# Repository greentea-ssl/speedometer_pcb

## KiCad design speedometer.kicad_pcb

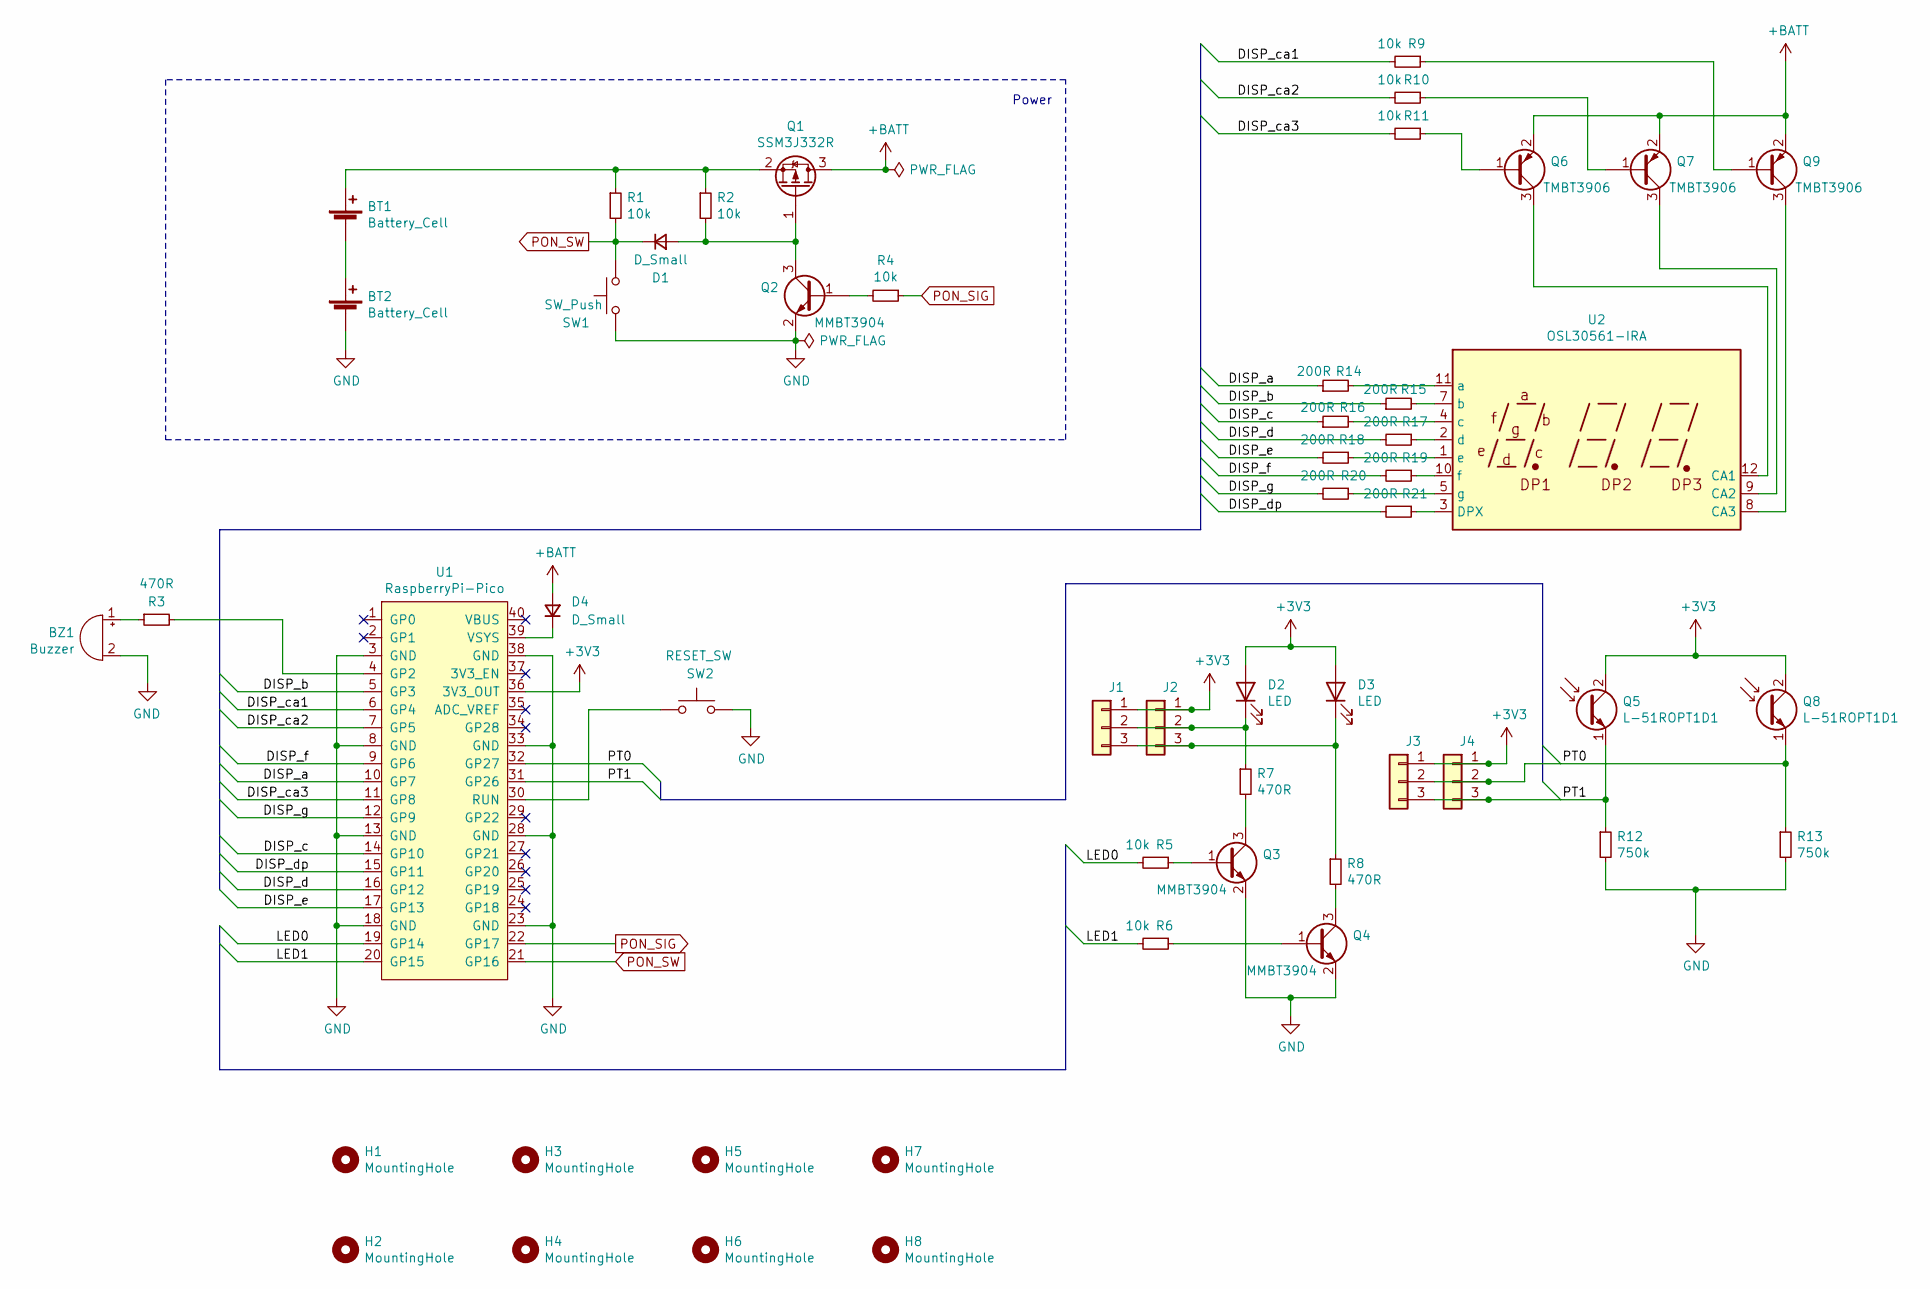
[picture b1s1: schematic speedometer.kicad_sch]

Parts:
BT1, BT2: Battery_Cell; AA-Battery
BZ1: Buzzer; Buzzer_TDK_PS1240P02BT_D12.2mm_H6.5mm
D1: D_Small; D_SOD-123
D2, D3: LED; LED_D5.0mm_IRGrey
D4: D_Small; D_0603_1608Metric
H1, H2, H3, H4, H5, H6, H7, H8: MountingHole; MountingHole_3.2mm_M3_noResist
J1, J2, J3, J4: Conn_01x03; JST_PH_S3B-PH-K_1x03_P2.00mm_Horizontal
Q1: SSM3J332R; SOT-23
Q2, Q3, Q4: MMBT3904; SOT-23
Q5, Q8: L-51ROPT1D1; LED_D5.0mm_IRBlack
Q6, Q7, Q9: TMBT3906; SOT-23
R1, R2, R4, R5, R6, R9, R10, R11: 10k; R_0603_1608Metric
R3, R7, R8: 470R; R_0603_1608Metric
R12, R13: 750k; R_0603_1608Metric
R14, R15, R16, R17, R18, R19, R20, R21: 200R; R_0603_1608Metric
SW1: SW_Push; SW_PUSH_6mm_H7.3mm
SW2: RESET_SW; SW_PUSH_6mm_H7.3mm
U1: RaspberryPi-Pico
U2: OSL30561-IRA

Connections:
+3V3: D2.2 (A), D3.2 (A), J1.1, J2.1, J3.1, J4.1, Q5.2 (C), Q8.2 (C), U1.36 (3V3_OUT)
+BATT: D4.2 (A), Q1.3 (D), Q6.2 (E), Q7.2 (E), Q9.2 (E)
/DISP_a: R14.1, U1.10 (GP7)
/DISP_b: R15.1, U1.5 (GP3)
/DISP_c: R16.1, U1.14 (GP10)
/DISP_ca1: R9.2, U1.6 (GP4)
/DISP_ca2: R10.2, U1.7 (GP5)
/DISP_ca3: R11.2, U1.11 (GP8)
/DISP_d: R17.2, U1.16 (GP12)
/DISP_dp: R21.2, U1.15 (GP11)
/DISP_e: R18.2, U1.17 (GP13)
/DISP_f: R19.2, U1.9 (GP6)
/DISP_g: R20.2, U1.12 (GP9)
/LED0: R5.2, U1.19 (GP14)
/LED1: R6.2, U1.20 (GP15)
/PT0: J3.2, J4.2, Q8.1 (E), R13.1, U1.32 (GP27)
/PT1: J3.3, J4.3, Q5.1 (E), R12.1, U1.31 (GP26)
GND: BT2.2 (-), BZ1.2 (+), Q2.2 (E), Q3.2 (E), Q4.2 (E), R12.2, R13.2, SW1.1, SW2.2, U1.3 (GND), U1.8 (GND), U1.13 (GND), U1.18 (GND), U1.23 (GND), U1.28 (GND), U1.33 (GND), U1.38 (GND)
unnamed: BT1.1 (+), Q1.2 (S), R1.1, R2.1
unnamed: BT1.2 (-), BT2.1 (+)
unnamed: BZ1.1 (-), R3.1
unnamed: D1.2 (A), Q1.1 (G), Q2.3 (C), R2.2
unnamed: D2.1 (K), J1.2, J2.2, R7.1
unnamed: D3.1 (K), J1.3, J2.3, R8.1
unnamed: D4.1 (K), U1.39 (VSYS)
unnamed: Q2.1 (B), R4.2
unnamed: Q3.1 (B), R5.1
unnamed: Q3.3 (C), R7.2
unnamed: Q4.1 (B), R6.1
unnamed: Q4.3 (C), R8.2
unnamed: Q6.1 (B), R11.1
unnamed: Q6.3 (C), U2.12 (CA1)
unnamed: Q7.1 (B), R10.1
unnamed: Q7.3 (C), U2.9 (CA2)
unnamed: Q9.1 (B), R9.1
unnamed: Q9.3 (C), U2.8 (CA3)
unnamed: R3.2, U1.4 (GP2)
unnamed: SW2.1, U1.30 (RUN)
unnamed: R21.1, U2.3 (DPX)
unnamed: R14.2, U2.11 (a)
unnamed: R15.2, U2.7 (b)
unnamed: R16.2, U2.4 (c)
unnamed: R17.1, U2.2 (d)
unnamed: R18.1, U2.1 (e)
unnamed: R19.1, U2.10 (f)
unnamed: R20.1, U2.5 (g)
PON_SIG: R4.1, U1.22 (GP17)
PON_SW: D1.1 (K), R1.2, SW1.2, U1.21 (GP16)

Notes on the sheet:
Power

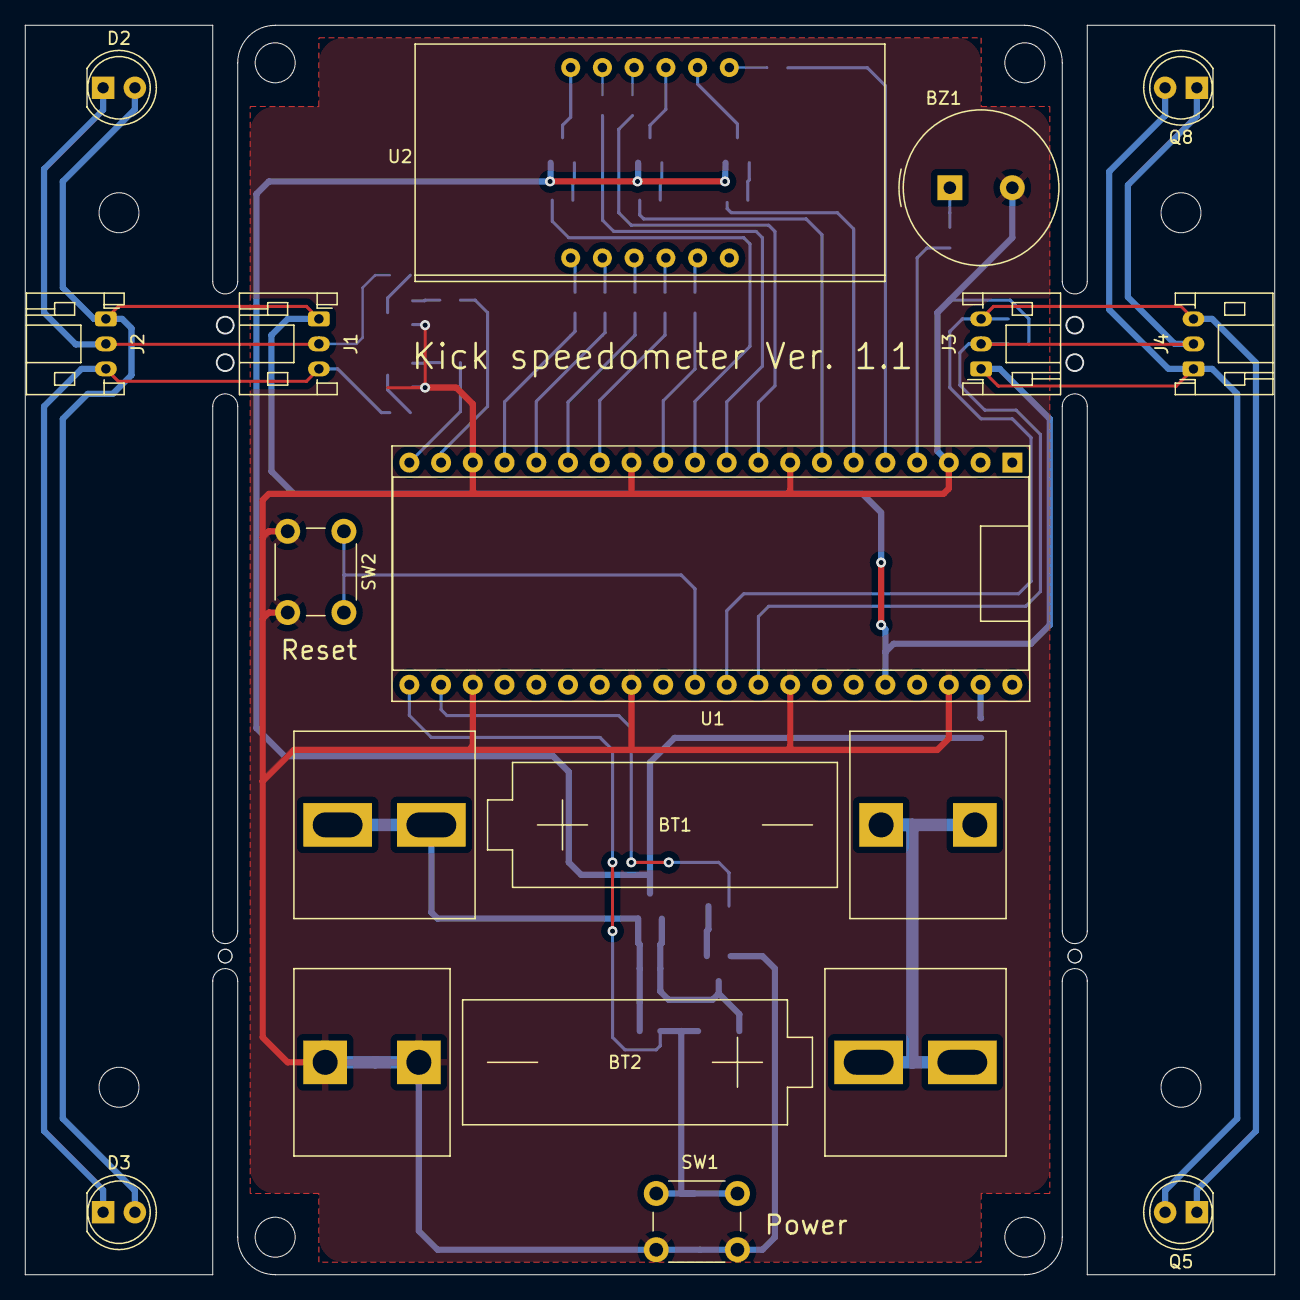
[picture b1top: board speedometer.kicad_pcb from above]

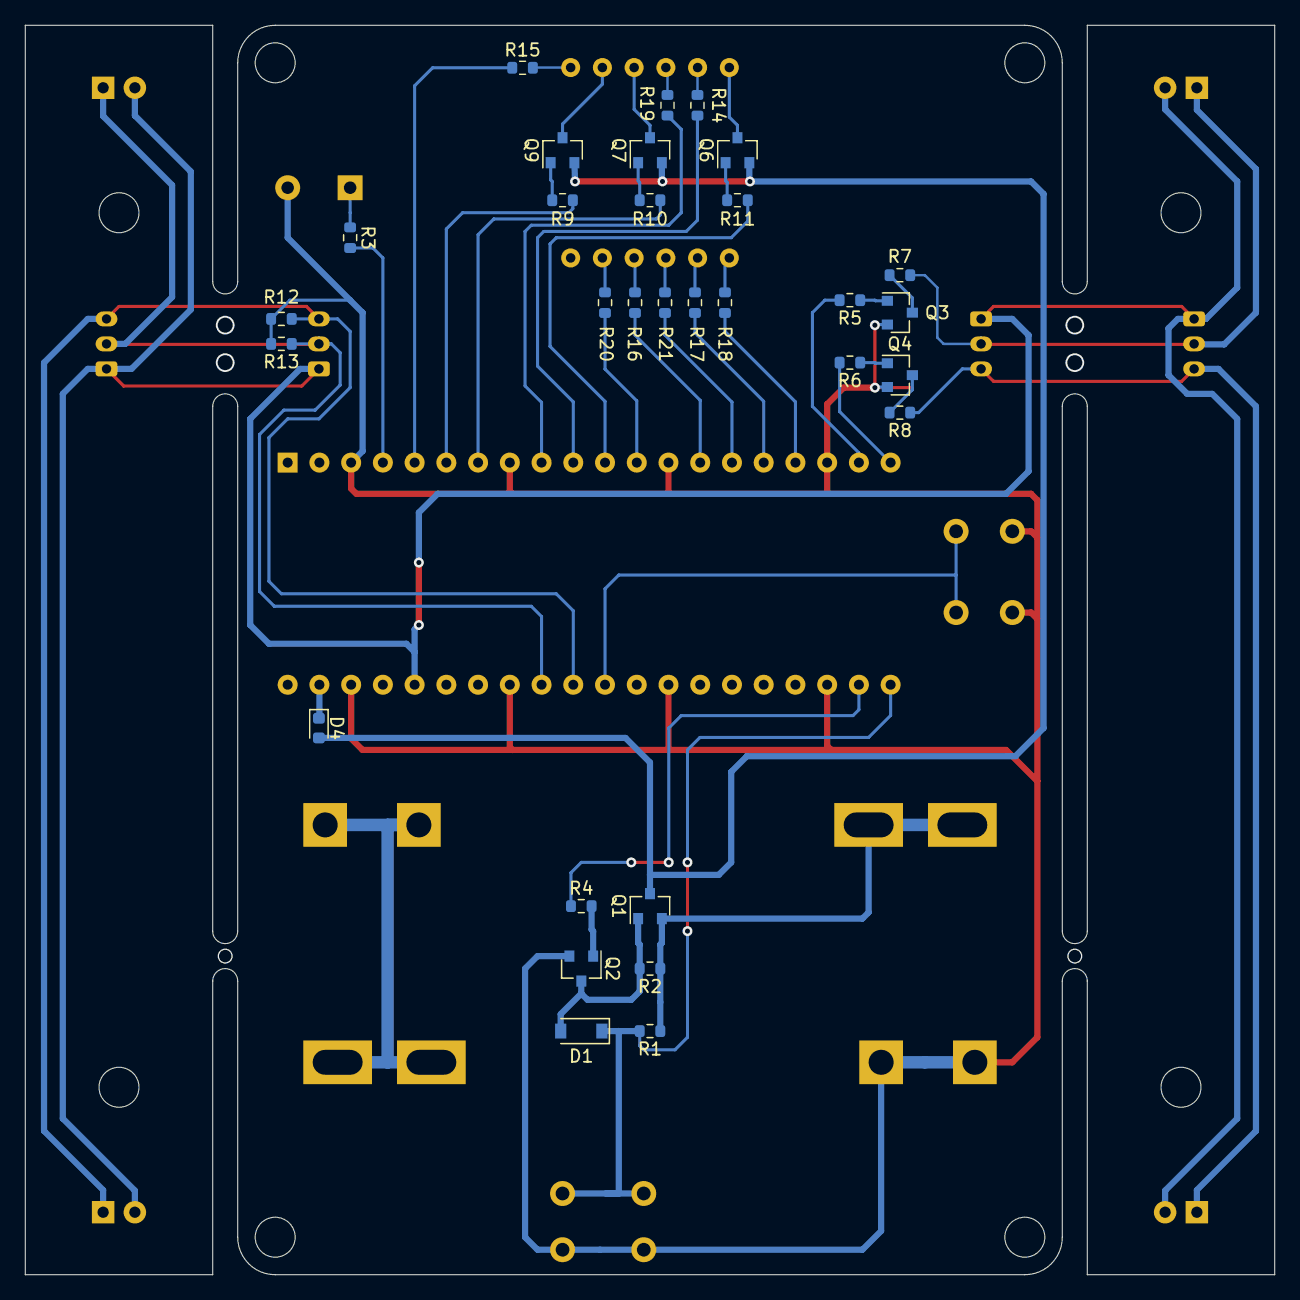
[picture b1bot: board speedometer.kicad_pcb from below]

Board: 2 copper layers, 100.0 x 100.0 mm, 53 parts (30 on the bottom side), 48 nets.

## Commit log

2025-04-14 回路図まで完成
2025-04-14 ガーバー書き出し
2025-04-14 アートワーク完成
2025-04-26 v1.0での手修正部分を反映
